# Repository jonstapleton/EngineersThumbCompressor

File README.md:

# EngineersThumbCompressor

NOTE: This project is not yet complete. Do not, under any circumstances, trust the documents made available here as there is no proof that they actually work.

This project is a full build of the Engineer's Thumb Compression pedal, found at http://valvewizard.co.uk/engineersthumb2.html. The circuit design is copied from this site. The board design, enclosure, and digital control circuit are all added on to the original design. 

For a full BOM with links, follow this link: https://docs.google.com/spreadsheets/d/15msUTMszm6xk95Vp56AjPnUBffsZkzXK5lIhBhOD9lE/edit?usp=sharing. This document will be updated as the project is iterated.

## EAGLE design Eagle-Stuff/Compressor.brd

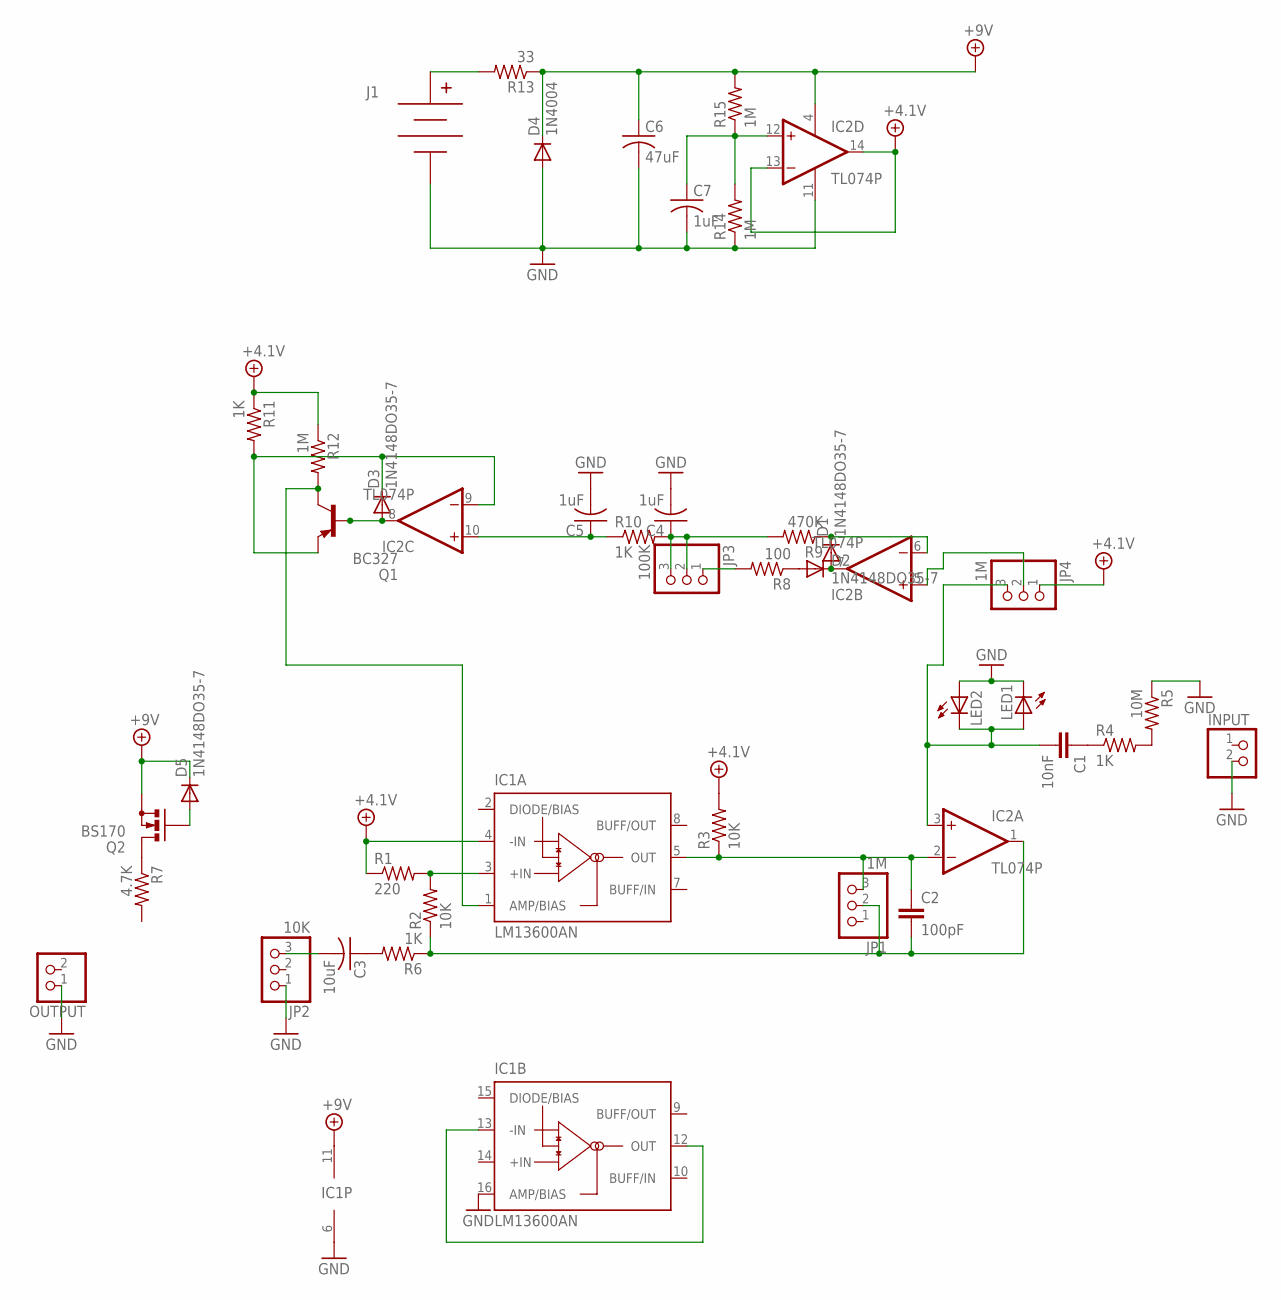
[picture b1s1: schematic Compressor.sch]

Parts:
C1: 10nF; C025-030X050
C2: 100pF; C025-030X050
C3: 10uF; C025-040X050
C4, C5, C7: 1uF; C025-040X050
C6: 47uF; C025-040X050
D1, D2, D3, D5: 1N4148DO35-7; DO35-7
D4: 1N4004; DO41-10
IC1: LM13600AN; DIL16
IC2: TL074P; DIL14
INPUT: PINHD-1X2; 1X02
J1: BC9VPC
JP1, JP4: 1M; 1X03
JP2: 10K; 1X03
JP3: 100K; 1X03
LED1, LED2: LEDLZR181; LZR181
OUTPUT: PINHD-1X2; 1X02
Q1: BC327; TO92
Q2: BS170; SOT54E
R1: 220; 0207/7
R2, R3: 10K; 0207/7
R4, R6, R10, R11: 1K; 0207/7
R5: 10M; 0207/7
R7: 4.7K; 0207/7
R8: 100; 0207/7
R9: 470K; 0207/7
R12, R14, R15: 1M; 0207/7
R13: 33; 0207/7

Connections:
+4.1V: IC1.4 (-IN), IC2.13 (-IN), IC2.14 (OUT), JP4.1, R1.1, R3.2, R11.1, R12.1
+9V: C6.1, D4.C, D5.C, IC1.11 (V+), IC2.4 (V+), Q2.S, R13.1, R15.2
GND: C4.2, C5.2, C6.2, C7.2, D4.A, IC1.6 (V-), IC1.16 (AMP/BIAS), IC2.11 (V-), INPUT.2, J1.V-, JP2.1, LED1.K (C), LED2.A, OUTPUT.1, R5.1, R14.1
unnamed: IC1.3 (+IN), R1.2, R2.2
unnamed: IC1.12 (OUT), IC1.13 (-IN)
unnamed: C2.1, IC1.5 (OUT), IC2.2 (-IN), JP1.3, R3.1
unnamed: D1.A, D2.C, IC2.7 (OUT)
unnamed: C1.1, R4.1
unnamed: R4.2, R5.2
unnamed: C1.2, IC2.3 (+IN), JP4.3, LED1.A, LED2.K (C)
unnamed: D1.C, IC2.6 (-IN), R9.1
unnamed: C2.2, IC2.1 (OUT), JP1.2, R2.1, R6.1
unnamed: C3.1, R6.2
unnamed: C3.2, JP2.3
unnamed: D2.A, R8.1
unnamed: JP3.1, R8.2
unnamed: C4.1, JP3.2, JP3.3, R9.2, R10.2
unnamed: C7.1, IC2.12 (+IN), R14.2, R15.1
unnamed: C5.1, IC2.10 (+IN), R10.1
unnamed: D3.A, IC2.8 (OUT), Q1.2 (B)
unnamed: D3.C, IC2.9 (-IN), Q1.1 (E), R11.2
unnamed: J1.V+, R13.2
unnamed: IC1.1 (AMP/BIAS), Q1.3 (C), R12.2
unnamed: D5.A, Q2.G
unnamed: Q2.D, R7.1
unnamed: IC2.5 (+IN), JP4.2

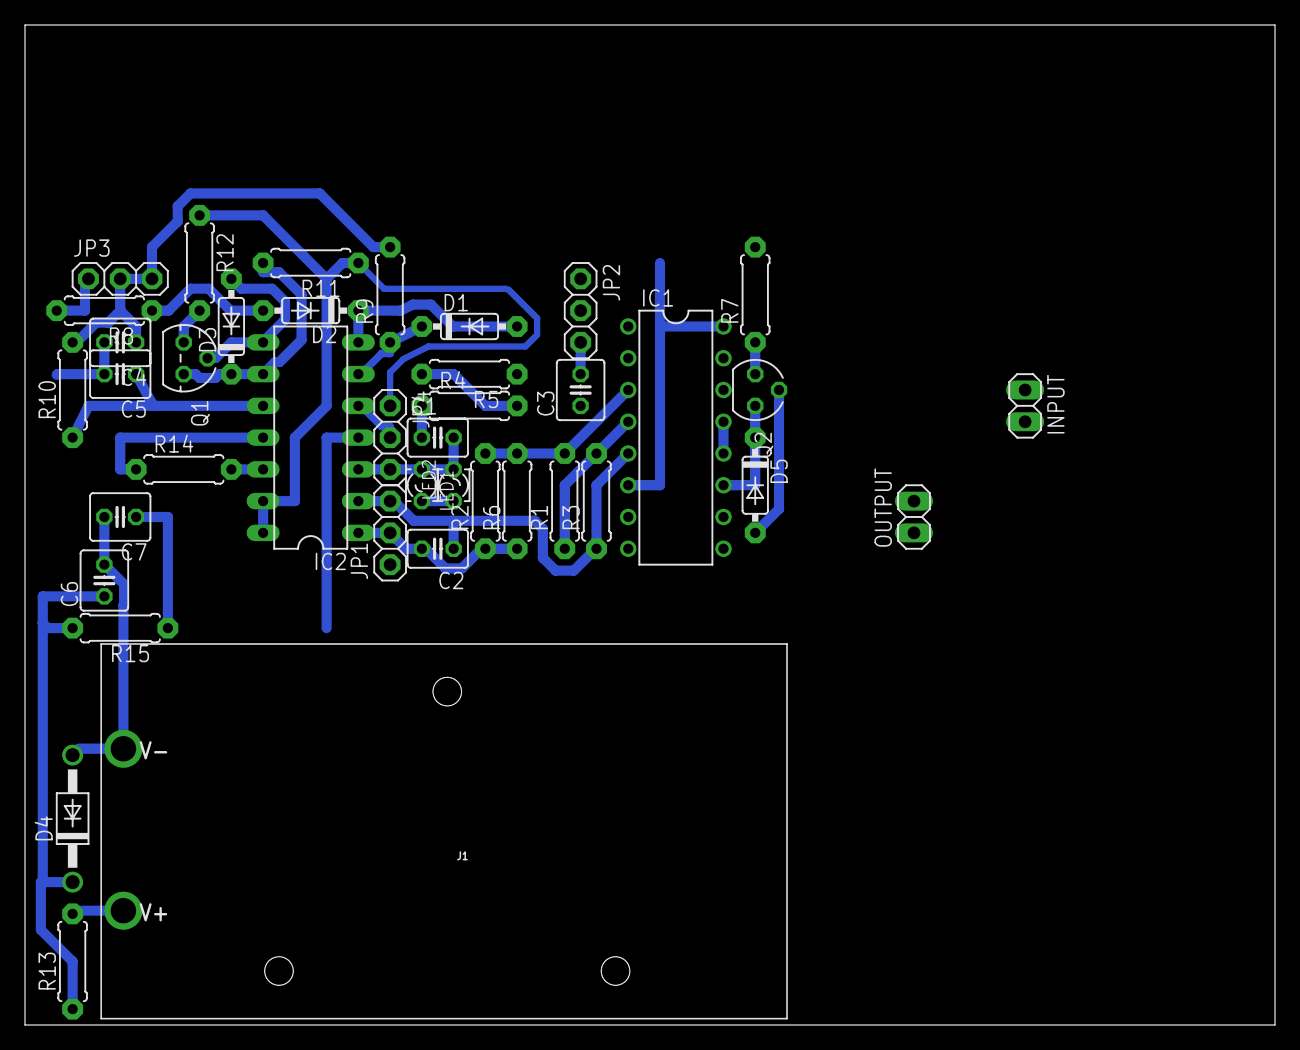
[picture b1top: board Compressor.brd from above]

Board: 2 copper layers, 100.0 x 80.0 mm, 40 parts (0 on the bottom side), 26 nets.

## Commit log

2017-08-12 Initial board and schematic commit
    Need to add switches and jacks, bass modification, attack potentiometer, check for sidechain configuration.

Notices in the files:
parts and their libraries:
SparkFun-Connectors: Licensing: Creative Commons ShareAlike 4.0 International - https://creativecommons.org/licenses/by-sa/4.0
